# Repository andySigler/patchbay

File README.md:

# Patchbay

## A Wireless Framework for Musical Instruments and Toys

This was built so that I could <b>very</b> easily create peer-to-peer connections between my physical computing projects, both old and new. The idea is to lower the barrier to entry for a project to become wireless and interoperable, using a wireless protocol inspired by MIDI, and device-specific Bluetooth LE profiles, auto-generated for each project.

Originally developed for my [ITP '14 masters thesis](http://www.andysigler.com/patchbay/), I have rebuilt it from the ground up during my residency at ITP this past year.

## Using Patchbay

#### Wiring

The Patchbay breakout board connects over hardware SPI, which are pins `D13`, `D12`, and `D11` on the Arduino Uno. The breakout also uses pins `D10`, `D9`, `D8`, `D7`, and `D2` for SPI handshaking with both radios, and one additional reset pin for the nRF51822.

On the Arduino Uno, this leaves digital pins `D0`, `D1`, `D3`, `D4`, `D5`, and `D6` available, as well as all Analog pins.

#### Initialize

Include the Patchbay library in your Arduino sketch, and initialize it with the mesh ID, the name of your device, and the number of physical `inputs` and `outputs` you would like it to expose.

```arduino
#include <Patchbay.h>

#define ID 					1
#define total_inputs 		2
#define total_outputs 		1

Patchbay myPatch( ID , "Device-Name" , total_inputs , total_outputs );
```

All `inputs` and `outputs` are stored in two arrays for each type, and each is referenced through the API by their index. This means that if you have three `inputs`, the first has an identifier of `0`, the second `1`, and so on.

#### Setup

Once initialzed at the top of your sketch, simple call `.begin()` inside of the Arduino `setup()` function. This function will begin SPI communication with both radios, set your network ID, as well as setup your device's custom GATT profile.

```arduino
void setup(){
	myPatch.begin();
}
```

#### Naming an `input` or `output`

`inputs` and `outputs` can be assigned names to show up in the Patchbay interface. These are strings or char arrays of less than 20 characters. Names should be assigned once inside the Arduino `setup()` function.

```arduino
myPatch.inputName( 0 , "knob-1");
myPatch.inputName( 1 , "knob-2");

myPatch.outputName( 0 , "LED");
```

#### Update

Patchbay relies on very fast communication and update cycles with the breakout board. `.update()` handles all of this for you, checking for any BLE connections and updates, as well sending and receiving any necessary data over the RFm69.

Call `.update()` as often as possible. If your sketch uses any blocking functions, either try and avoid it, or call `.update()` multiple times inside your `loop()`.

```arduino
void loop(){
	myPatch.update();
}
```

`.update()` will also return a `boolean` for whether this devices' `outputs` have received a new value. If it returns `true`, your code should read the `output` values and handle them in whatever way your sketch needs to.

```arduino
void loop(){
	if(myPatch.update()) {
		// update your sketch as necessary
	}
}
```

#### Write to `inputs`

Patchbay `inputs` can be physical inputs like sensors, and must be represented as an integer between `0` and `255`.

```arduino
int knob_1_value = analogRead(0) / 4;			// map the value to 0-255
int knob_2_value = analogRead(1) / 4;
```

An `input` is then written to, and automatically sent out over any wireless links that might exist.

```arduino
myPatch.inputWrite( 0 , knob_1_value );			// set the values
myPatch.inputWrite( 1 , knob_2_value );

myPatch.update();								// send the values wireless
```

#### Read from `outputs`

Patchbay `outputs` can be physical outputs like lights or motors, and must be represented as an integer between `0` and `255`.

```arduino
int new_LED_value = myPatch.outputRead( 0 );	// get the value
```

When an `outputs` value has been updated, `.update()` will return true, allowing the sketch to update physical outputs only when necessary.

In addition, each `output` can be tested to see if it has changed or not with the `.outputChanged()` function. This is useful if your sketch has multiple `outputs`.

```arduino
if( myPatch.update() ) {						// update all radio communications

	for( int i=0; i<total_outputs; i++ ) {		// loop through all outputs

		if( myPatch.outputChanged( i ) ) {		// test to see if this one has changed

			Serial.print("Output ");			// use the new value
			Serial.print(i);
			Serial.print(" has changed to ");
			Serial.println( myPatch.outputRead(i) );
		}
	}
}
```

## Shoulders of Giants

I have developed Patchbay so far on my own in my free time, and none of this would have been possible without the wonderful open-source software and hardware from the following people.

The Arduino library currently depends on LowPowerLab's [RFm69 library](https://github.com/lowpowerlab/rfm69), and Adafruit's Bluefruit LE [firmware](https://github.com/adafruit/Adafruit_BluefruitLE_Firmware) and [library](https://github.com/adafruit/Adafruit_BluefruitLE_nRF51).

The HTML5 interface uses [hammer.js](http://hammerjs.github.io/) for touch events, and connects over BLE using Rand Dusing's [cordova plugin](https://github.com/randdusing/BluetoothLE), allowing the app to be available on iOS and Android.

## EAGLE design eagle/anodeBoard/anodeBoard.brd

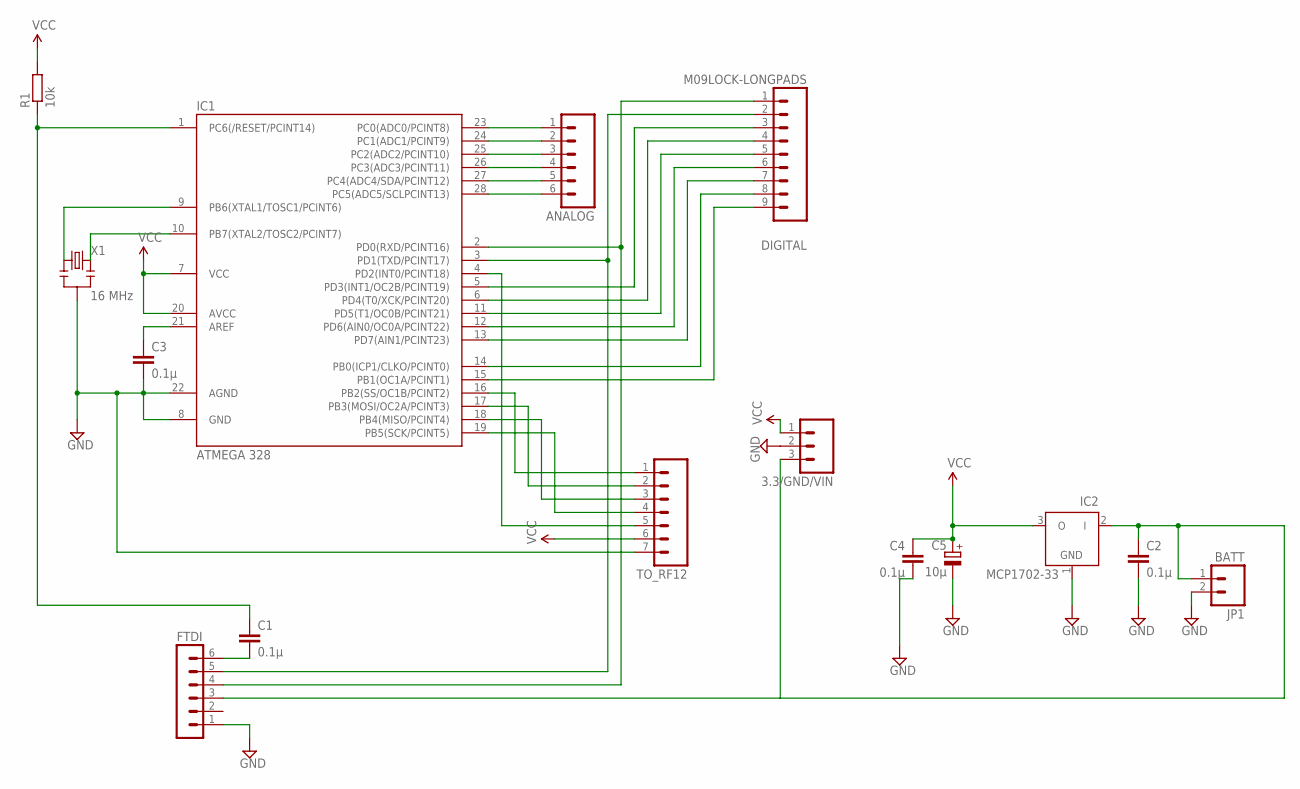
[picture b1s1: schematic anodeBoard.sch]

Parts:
3.3/GND/VIN: M03LOCK_LONGPADS; 1X03_LOCK_LONGPADS
ANALOG: M06LOCK_LONGPADS; 1X06_LOCK_LONGPADS
C1, C2, C3, C4: 0.1µ; C025-024X044
C5: 10µ; E1,8-4
DIGITAL: M09LOCK-LONGPADS; 1X09_LOCK_LONGPADS
FTDI: FTDI; MA06-1
IC1: ATMEGA 328; DIL28-3
IC2: MCP1702-33; TO92
JP1: BATT; 1X02_LOCK_LONGPADS
R1: 10k; 0204/7
TO_RF12: M07LOCK_LONGPADS; 1X07_LOCK_LONGPADS
X1: 16 MHz; RESONATOR-PTH

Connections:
GND: 3.3/GND/VIN.2, C2.2, C3.2, C4.2, C5.-, FTDI.1, IC1.8 (GND), IC1.22 (AGND), IC2.1 (GND), JP1.2, TO_RF12.7, X1.2
unnamed: IC1.9 (PB6(XTAL1/TOSC1/PCINT6)), X1.1
unnamed: DIGITAL.3, IC1.5 (PD3(INT1/OC2B/PCINT19))
unnamed: DIGITAL.4, IC1.6 (PD4(T0/XCK/PCINT20))
unnamed: ANALOG.1, IC1.23 (PC0(ADC0/PCINT8))
unnamed: ANALOG.2, IC1.24 (PC1(ADC1/PCINT9))
unnamed: ANALOG.3, IC1.25 (PC2(ADC2/PCINT10))
unnamed: ANALOG.4, IC1.26 (PC3(ADC3/PCINT11))
unnamed: IC1.16 (PB2(SS/OC1B/PCINT2)), TO_RF12.1
unnamed: IC1.17 (PB3(MOSI/OC2A/PCINT3)), TO_RF12.2
unnamed: IC1.18 (PB4(MISO/PCINT4)), TO_RF12.3
unnamed: IC1.19 (PB5(SCK/PCINT5)), TO_RF12.4
unnamed: ANALOG.5, IC1.27 (PC4(ADC4/SDA/PCINT12))
unnamed: ANALOG.6, IC1.28 (PC5(ADC5/SCLPCINT13))
unnamed: IC1.4 (PD2(INT0/PCINT18)), TO_RF12.5
unnamed: DIGITAL.5, IC1.11 (PD5(T1/OC0B/PCINT21))
unnamed: DIGITAL.6, IC1.12 (PD6(AIN0/OC0A/PCINT22))
unnamed: DIGITAL.7, IC1.13 (PD7(AIN1/PCINT23))
unnamed: DIGITAL.8, IC1.14 (PB0(ICP1/CLKO/PCINT0))
unnamed: C3.1, IC1.21 (AREF)
unnamed: C1.2, FTDI.6
unnamed: IC1.10 (PB7(XTAL2/TOSC2/PCINT7)), X1.3
unnamed: DIGITAL.9, IC1.15 (PB1(OC1A/PCINT1))
PWR: 3.3/GND/VIN.3, C2.1, FTDI.3, IC2.2 (I), JP1.1
RST: C1.1, IC1.1 (PC6(/RESET/PCINT14)), R1.1
RXD: DIGITAL.1, FTDI.4, IC1.2 (PD0(RXD/PCINT16))
TXD: DIGITAL.2, FTDI.5, IC1.3 (PD1(TXD/PCINT17))
VCC: 3.3/GND/VIN.1, C4.1, C5.+, IC1.7 (VCC), IC1.20 (AVCC), IC2.3 (O), R1.2, TO_RF12.6

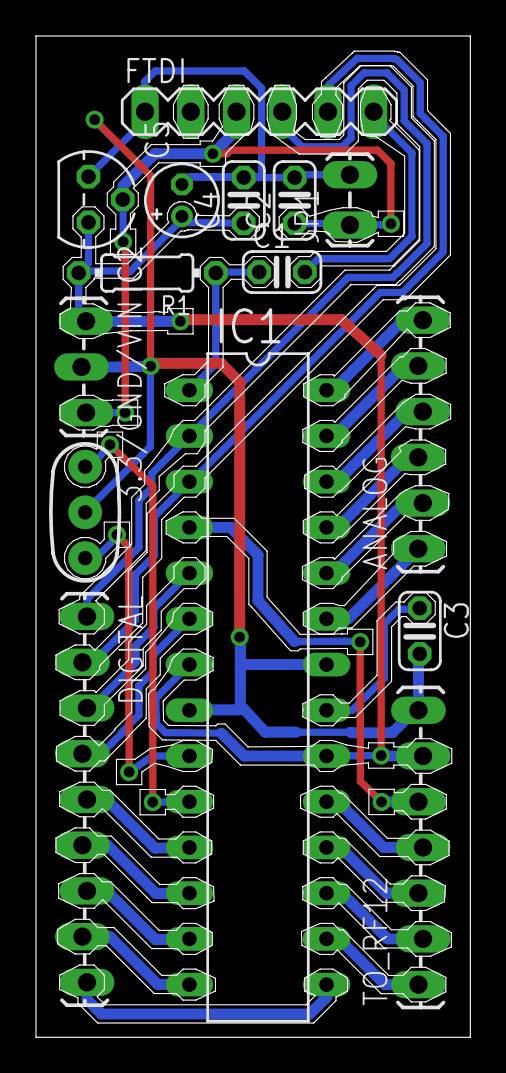
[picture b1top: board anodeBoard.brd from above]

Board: 2 copper layers, 24.1 x 55.6 mm, 15 parts (0 on the bottom side), 28 nets.

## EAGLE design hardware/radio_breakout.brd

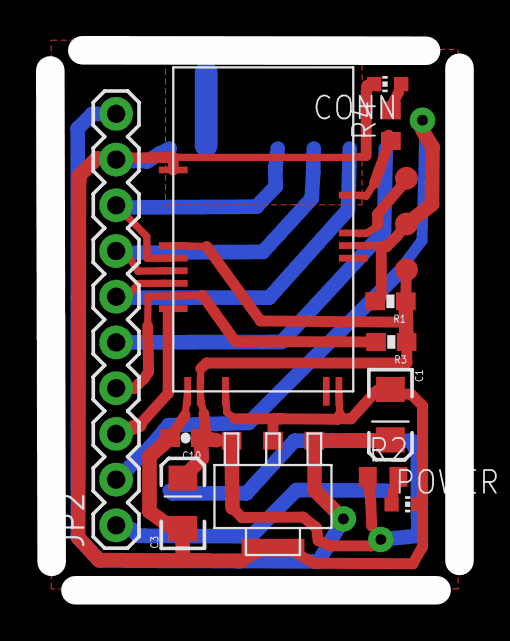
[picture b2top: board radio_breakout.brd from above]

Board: 2 copper layers, 22.7 x 30.0 mm, 16 parts (1 on the bottom side), 15 nets.

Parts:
C1, C3: 10uF; EIA3216
C10: 1uF; 0603-CAP
CLOCK, CLOCK1: PAD; SMD-ROUND
CONN: CHIP-LED0603
JP2: M10"; 1X10
POWER: CHIP-LED0603
R1, R3: 10k; 0603-RES
R2, R4: 10k; R0603
U$1: RFM69; S0C-RFM69
U$3: REGULATOR3.3V-UA78M33CDCYR; SOT223
U$5: NRF51-MDBT40-SPI; SOC-NRF51-MDBT40-SPI
VCC: PAD; SMD-ROUND

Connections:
BT-REQ: JP2.3, U$5.P0.25
BT-SS: JP2.4, R3.2, U$5.P0.24
GND: C1.C, C3.C, C10.2, CONN.C, JP2.9, POWER.C, U$1.GND, U$3.2, U$3.4, U$5.GND1, U$5.GND2, U$5.GND3, U$5.GND4, U$5.GND5, U$5.P0.30
MISO: JP2.7, U$1.MISO, U$5.P0.22
MOSI: JP2.6, U$1.MOSI, U$5.P0.23
unnamed: POWER.A, R2.2
unnamed: R4.1, U$5.P0.19
unnamed: CONN.A, R4.2
unnamed: CLOCK.P$1, U$5.SWCLK
RF-REQ: JP2.1, U$1.REQ
RF-SS: JP2.5, U$1.SS
SCK: JP2.8, U$1.SCK, U$5.P0.21
SWDIO/RST: CLOCK1.P$1, JP2.2, R1.2, U$5.SWDIO
VCC: C3.A, C10.1, R1.1, R2.1, R3.1, U$1.3.3V, U$3.3, U$5.AVDD, U$5.VDD, VCC.P$1
VIN: C1.A, JP2.10, U$3.1

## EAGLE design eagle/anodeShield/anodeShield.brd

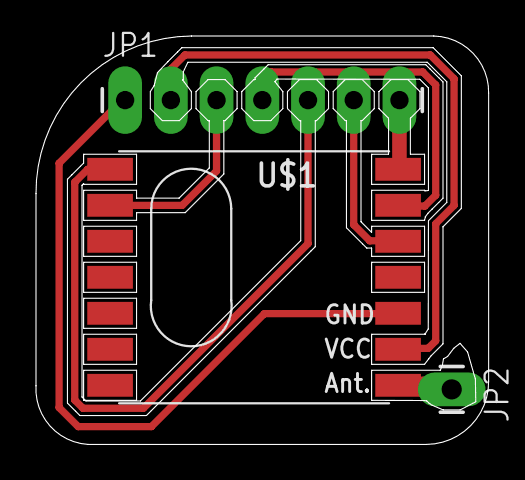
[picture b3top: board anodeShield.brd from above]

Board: 2 copper layers, 25.1 x 22.7 mm, 3 parts (0 on the bottom side), 8 nets.

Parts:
JP1: 1X07_LONGPADS
JP2: M01PTH_LONGPAD; 1X01_LONGPAD
U$1: RFM12B

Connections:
GND: JP1.1, U$1.GND
unnamed: JP1.7, U$1.SEL
unnamed: JP1.4, U$1.SCK
unnamed: JP1.6, U$1.SDI
unnamed: JP1.5, U$1.SDO
unnamed: JP1.3, U$1.IRQ
unnamed: JP2.1, U$1.ANT
VCC: JP1.2, U$1.VDD

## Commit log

2014-04-11 init commit
2014-04-11 no websockets
2014-04-11 yes websockets
2014-04-11 updated patchbay interactions
2014-04-28 separated circles
2014-05-14 booyah
2014-05-14 added arduino library and eagle files
2014-05-14 reorganized
2014-05-14 removed stuff
2014-05-14 nada
2014-05-14 adsf
2014-05-14 asdff
2014-05-14 added readme
2014-05-14 editting
2014-05-14 asdf
2014-05-14 stuff
2014-05-14 commented and added server arduino sketch
2014-05-14 thing
2014-05-14 farter
2014-05-20 updated README and added auto-connect to example folder
2015-07-10 moved most recent files to main repo
2015-07-10 updated Arduino library wordage and example
2015-07-10 updated arduino example
2015-07-10 readme update
2015-07-29 replaced UART with SPI bluefruit software and hardware
2015-08-15 update board files, arduino library, and readme
2015-08-15 udpated readme
2015-08-15 syntax highlighting
2015-08-15 added syntax highlighting
2015-08-15 added link to readme
2015-08-15 added wiring pic
2015-08-15 shrunk image
2015-08-15 replaced image
2015-08-15 image
2015-08-19 cordova app init, and simple BLE handling works
2015-08-19 displays node, and handles dooming and re-discovery
2015-08-20 basic read and write links works, but clumsily
2015-08-20 app passes early testing on iPad and iPhone
2015-08-20 library updates, including smoothing methods
2015-08-22 coord GUI bug fix, and scan refreshing for dooming
2015-08-22 added closing and ignoring function to help restore cached names
2015-08-22 changed broadcast interval to 15ms (faster)
2015-09-03 fixed 'doom' bug
2015-09-18 styling updates to the app (added title and button color)
2015-09-22 added "wait wheel" to email
2015-09-25 multiple-links bug removed, and BLE advertisement flag added to .begin()
2015-09-28 replace .setup() with correct .begin() in readme
2019-02-03 readme
2019-10-21 Changes link to personal website for thesis video

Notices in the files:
parts and their libraries:
SparkFun-Connectors: Licensing: CC v3.0 Share-Alike You are welcome to use this library for commercial purposes.
SparkFun-Capacitors: Licensing: Creative Commons ShareAlike 4.0 International - https://creativecommons.org/licenses/by-sa/4.0
